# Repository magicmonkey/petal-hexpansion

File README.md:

A "petal" hexpansion for the EMFcamp Tildagon badge.

It has 3 bands of LEDs which are individually controllable via I2C, using the AL5887 chip.

PCB schematics are in this repo, and the badge app software is in https://github.com/magicmonkey/petal-hexpansion-software

Use the "Petals" app in the badge app store to see some LED animations.

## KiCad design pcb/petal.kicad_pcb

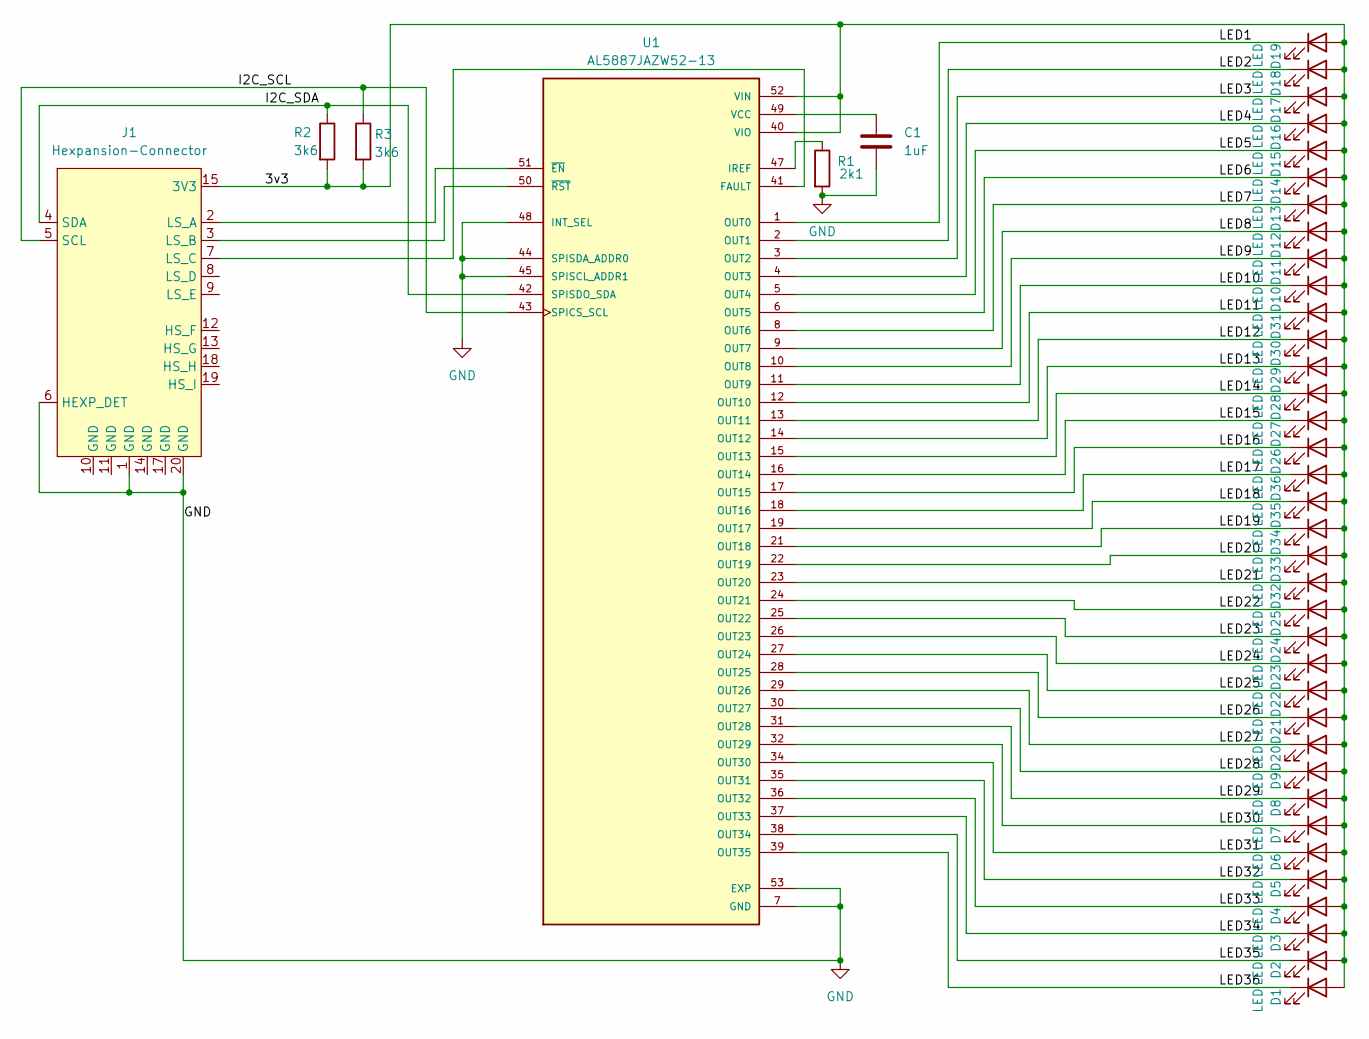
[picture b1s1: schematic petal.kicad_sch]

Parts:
C1: 1uF; C_0603_1608Metric
D1, D2, D3, D4, D5, D6, D7, D8, D9, D10, D11, D12, D13, D14, D15, D16, D17, D18, D19, D20, D21, D22, D23, D24, D25, D26, D27, D28, D29, D30, D31, D32, D33, D34, D35, D36: LED; LED_0603_1608Metric
J1: Hexpansion-Connector; hexpansion-edge-connector
R1: 2k1; R_0603_1608Metric
R2, R3: 3k6; R_0603_1608Metric
U1: AL5887JAZW52-13; IC_AL5887JAZW52-13; PARTREV 4-2

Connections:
/3v3: D1.2 (A), D2.2 (A), D3.2 (A), D4.2 (A), D5.2 (A), D6.2 (A), D7.2 (A), D8.2 (A), D9.2 (A), D10.2 (A), D11.2 (A), D12.2 (A), D13.2 (A), D14.2 (A), D15.2 (A), D16.2 (A), D17.2 (A), D18.2 (A), D19.2 (A), D20.2 (A), D21.2 (A), D22.2 (A), D23.2 (A), D24.2 (A), D25.2 (A), D26.2 (A), D27.2 (A), D28.2 (A), D29.2 (A), D30.2 (A), D31.2 (A), D32.2 (A), D33.2 (A), D34.2 (A), D35.2 (A), D36.2 (A), J1.15 (3V3), J1.16 (3V3), R2.2, R3.2, U1.40 (VIO), U1.52 (VIN)
/I2C_SCL: J1.5 (SCL), R3.1, U1.43 (SPICS_SCL)
/I2C_SDA: J1.4 (SDA), R2.1, U1.42 (SPISDO_SDA)
/LED1: D19.1 (K), U1.1 (OUT0)
/LED2: D18.1 (K), U1.2 (OUT1)
/LED3: D17.1 (K), U1.3 (OUT2)
/LED4: D16.1 (K), U1.4 (OUT3)
/LED5: D15.1 (K), U1.5 (OUT4)
/LED6: D14.1 (K), U1.6 (OUT5)
/LED7: D13.1 (K), U1.8 (OUT6)
/LED8: D12.1 (K), U1.9 (OUT7)
/LED9: D11.1 (K), U1.10 (OUT8)
/LED10: D10.1 (K), U1.11 (OUT9)
/LED11: D31.1 (K), U1.12 (OUT10)
/LED12: D30.1 (K), U1.13 (OUT11)
/LED13: D29.1 (K), U1.14 (OUT12)
/LED14: D28.1 (K), U1.15 (OUT13)
/LED15: D27.1 (K), U1.16 (OUT14)
/LED16: D26.1 (K), U1.17 (OUT15)
/LED17: D36.1 (K), U1.18 (OUT16)
/LED18: D35.1 (K), U1.19 (OUT17)
/LED19: D34.1 (K), U1.21 (OUT18)
/LED20: D33.1 (K), U1.22 (OUT19)
/LED21: D32.1 (K), U1.23 (OUT20)
/LED22: D25.1 (K), U1.24 (OUT21)
/LED23: D24.1 (K), U1.25 (OUT22)
/LED24: D23.1 (K), U1.26 (OUT23)
/LED25: D22.1 (K), U1.27 (OUT24)
/LED26: D21.1 (K), U1.28 (OUT25)
/LED27: D20.1 (K), U1.29 (OUT26)
/LED28: D9.1 (K), U1.30 (OUT27)
/LED29: D8.1 (K), U1.31 (OUT28)
/LED30: D7.1 (K), U1.32 (OUT29)
/LED31: D6.1 (K), U1.34 (OUT30)
/LED32: D5.1 (K), U1.35 (OUT31)
/LED33: D4.1 (K), U1.36 (OUT32)
/LED34: D3.1 (K), U1.37 (OUT33)
/LED35: D2.1 (K), U1.38 (OUT34)
/LED36: D1.1 (K), U1.39 (OUT35)
GND: C1.2, J1.1 (GND), J1.6 (HEXP_DET), J1.20 (GND), R1.2, U1.7 (GND), U1.20 (GND), U1.33 (GND), U1.44 (SPISDA_ADDR0), U1.45 (SPISCL_ADDR1), U1.46 (GND), U1.48 (INT_SEL), U1.53 (EXP)
unnamed: J1.2 (LS_A), U1.51 (~EN)
unnamed: J1.3 (LS_B), U1.50 (~RST)
unnamed: J1.7 (LS_C), U1.41 (FAULT)
unnamed: R1.1, U1.47 (IREF)
unnamed: C1.1, U1.49 (VCC)

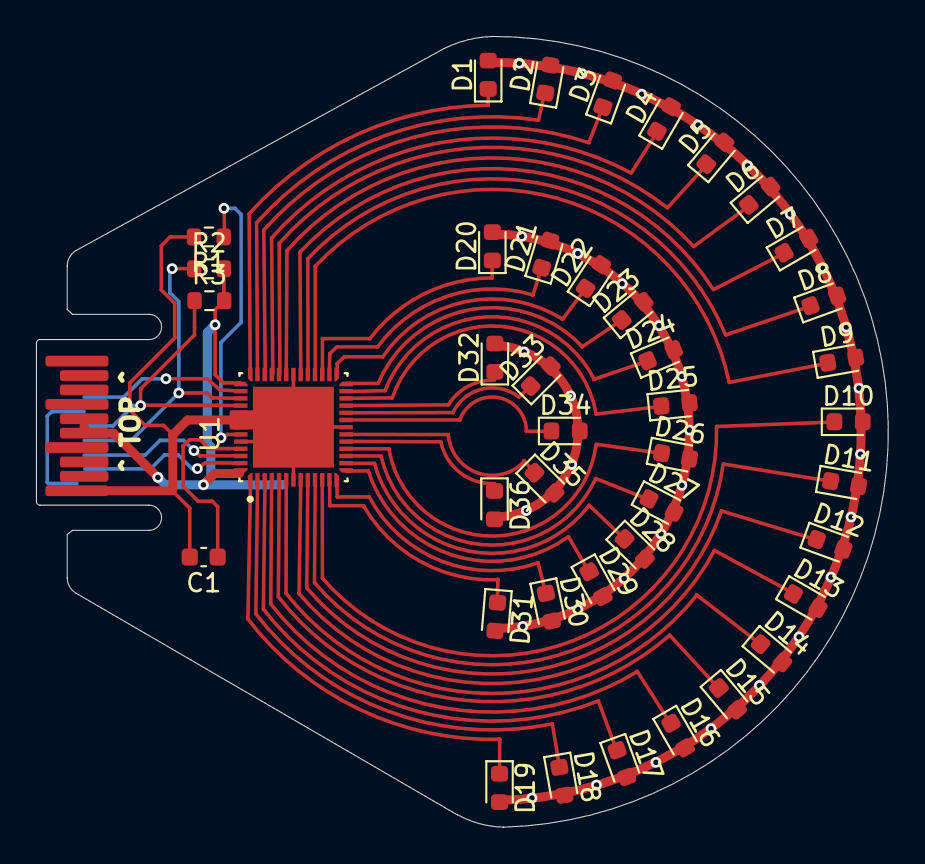
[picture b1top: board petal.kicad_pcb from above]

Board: 2 copper layers, 47.3 x 43.9 mm, 42 parts (0 on the bottom side), 45 nets.

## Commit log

2026-06-22 LEDs light up in port 4
2026-06-22 Upload instructions
2026-06-22 Moved the init so it only does it at app launch
2026-06-22 Also turn the LEDs off
2026-06-22 Balanced brightnesses
2026-06-22 Detect multiple petals
2026-06-23 Some animations for all 6 petals
2026-06-23 Some more animations
2026-06-26 Attempt to refactor
2026-06-26 Menu-driven
2026-06-27 Make room for the schematics
2026-06-27 Add some kind of set of schematic files
2026-06-27 readme
2026-06-27 Update the copy notes to include directory
2026-06-27 Create LICENSE
2026-06-27 Remove unneeded import
2026-06-27 Useful explanation for the magic number
2026-06-27 Finish port number refactoring
2026-06-27 Explain the brightness range
2026-06-27 Starting to allow multiple animations
2026-06-27 Auto-scan for animations
2026-06-27 Animations have names
2026-06-27 Allow background animations
2026-06-27 Confetti plugin: a set number of random led-on events
2026-06-27 Make each band equally likely
2026-06-27 Better app name
2026-06-27 Adjust for async and animation name features
2026-06-27 Independent bits of the animations
2026-06-27 Add decay function and remove loop limit
2026-06-27 Always start with no LEDs on
2026-06-27 A descriptive image
2026-06-27 Added an animated rainbow
2026-06-27 Reference the software repo in the readme
2026-06-27 Add the video to the readme
2026-06-27 App software has moved to "petal-hexpansion-software" repo
